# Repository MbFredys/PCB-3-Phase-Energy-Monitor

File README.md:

# Three-Phase Energy Monitor

Hardware design for a three-phase, four-wire energy-monitoring platform with Ethernet and Power over Ethernet, intended for future integration with building-management systems.

> **Project status:** Design and manufacturing documentation completed. The PCB has not been fabricated, calibrated, electrically validated, or tested for regulatory compliance.

## Project objective

The project explores an open and documented architecture capable of acquiring three-phase electrical measurements and exposing them through a connected embedded platform.

## System architecture

- **Measurement:** ATM90E32AS for 3P4W energy measurement
- **Controller:** ESP32-S3-MINI-1
- **Networking:** LAN8720A Ethernet PHY using RMII
- **Power:** TPS2378 PoE interface with local 5 V and 3.3 V rails
- **Sensing:** External current transformers and resistive voltage-sensing networks
- **Isolation:** Digital isolators between measurement and low-voltage digital domains
- **Development access:** USB and debugging/programming interfaces

## Engineering work

- Defined system requirements and functional architecture
- Selected the principal ICs, protection devices, connectors, and power components
- Developed the schematic and multi-domain PCB layout in KiCad
- Defined measurement, isolation, Ethernet, PoE, and power-distribution sections
- Prepared the BOM and manufacturing documentation

## Key design considerations

- Isolation boundaries and return-current paths
- Creepage and clearance around mains-related circuitry
- Mixed-signal grounding and decoupling
- Ethernet differential routing and PHY termination
- PoE power conversion and protection
- Calibration strategy for voltage and current channels

## Deliverables

The repository contains the available design source files and supporting manufacturing documentation. Review the repository structure before using any generated outputs.

## Validation still required

A physical prototype is required to verify:

- Electrical safety and isolation distances
- Measurement accuracy and calibration
- Ethernet and PoE operation
- Thermal behavior and power integrity
- EMC/EMI performance
- Compliance with any applicable product or installation standards

This repository should be treated as an engineering design project, not as a certified or production-ready energy meter.

## License

Licensed under CERN-OHL-W-2.0.

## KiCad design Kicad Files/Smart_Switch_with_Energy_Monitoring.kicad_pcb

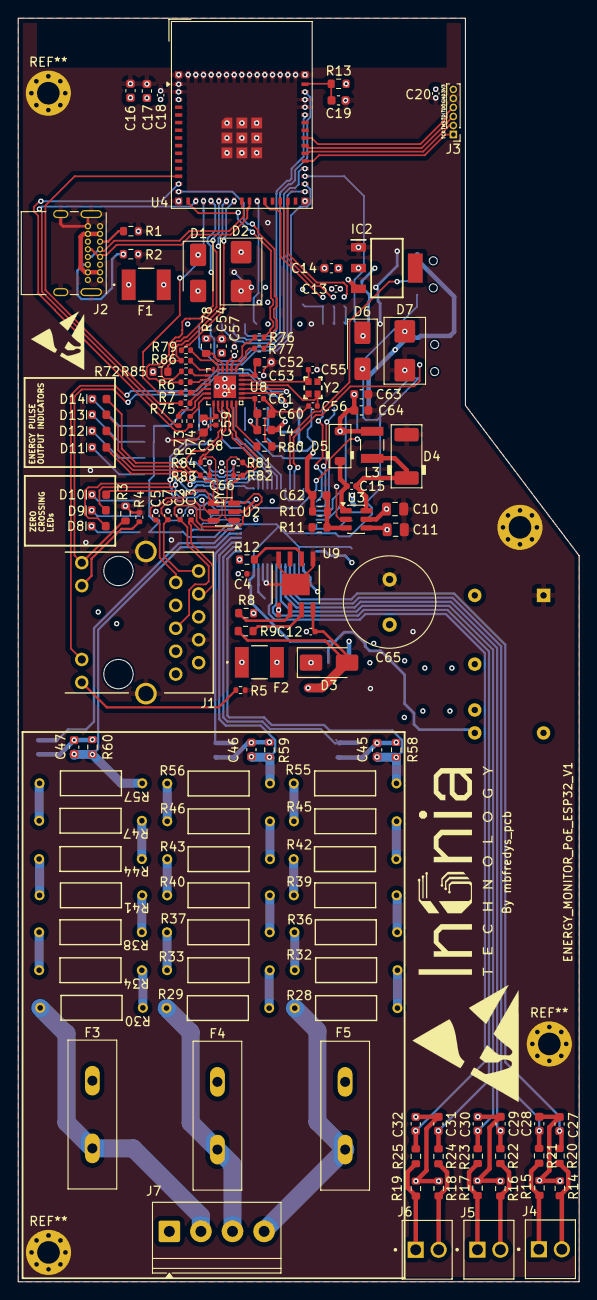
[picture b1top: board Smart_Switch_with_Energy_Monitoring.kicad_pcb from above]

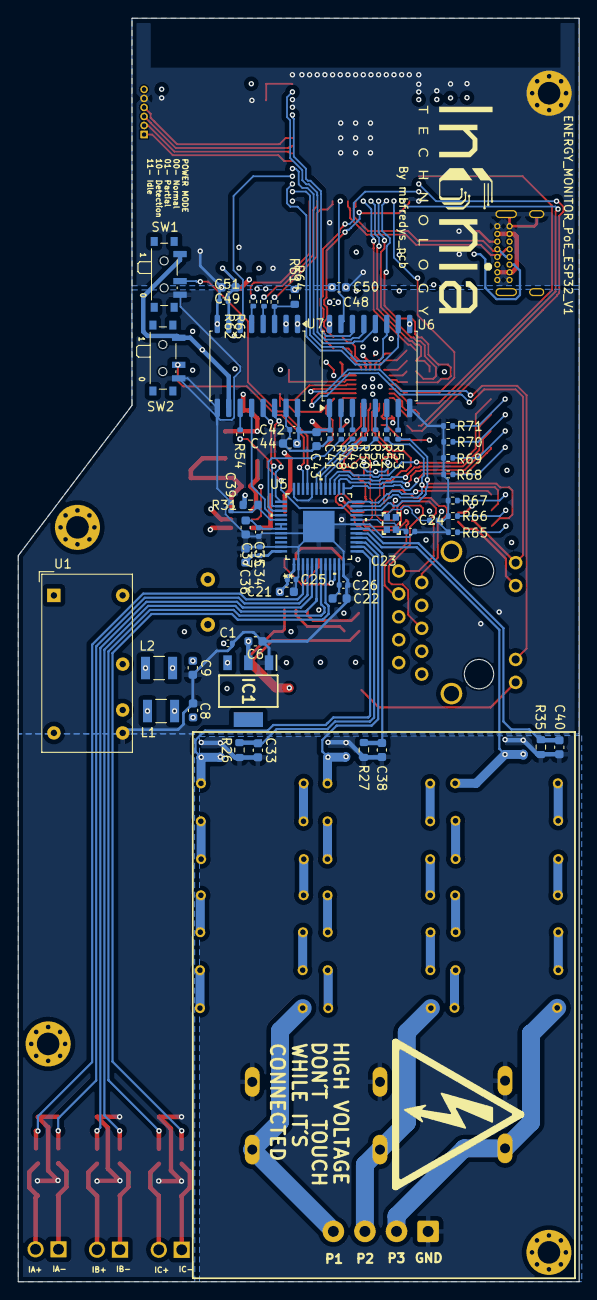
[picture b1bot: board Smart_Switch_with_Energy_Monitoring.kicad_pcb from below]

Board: 4 copper layers, 62.1 x 140.0 mm, 197 parts (58 on the bottom side), 153 nets.

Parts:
C1, C4, C12, C13, C15, C18, C20, C25, C26, C34, C35, C39, C41, C42, C48, C49, C57, C66: 0.1uF; C_0402_1005Metric
C2, C3, C5, C7, C23, C24, C55, C56: 10pF; C_0402_1005Metric
C6, C14, C16, C21, C36, C37, C43, C44, C50, C51, C54, C63, C64: 10uF; C_0603_1608Metric
C8, C9: 2.2uF; C_0603_1608Metric
C10, C11: 10uF; C_0805_2012Metric
C17, C19, C52, C58, C60: 1uF; C_0603_1608Metric
C22: 4.7uF; C_0603_1608Metric
C27, C28, C29, C30, C31, C32, C33, C38, C40, C45, C46, C47: 18nF; C_0603_1608Metric
C53, C59, C61: 470pF; C_0402_1005Metric
C62: 20pF; C_0603_1608Metric
C65: 22uF; C_Radial_D10.0mm_H12.5mm_P5.00mm
D1, D6: SS14; D_SMA
D2, D7: SMBJ5.0CA; D_SMB_TVS
D3: SMAJ58A; D_SMA
D4: SM360; D_MELF
D5: 1N4148W; D_SOD-123
D8, D9, D10, D11, D12, D13, D14: LEDs; LED_0603_1608Metric
F1: 1812L110PR; FUSE_1812L05060_LTF
F2: 1812L050/60MR; FUSE_1812L05060_LTF
F3, F4, F5: MOV14D471K
IC1, IC2: LD1117-3.3V; SOT230P700X180-4N
J1: RJ45_PoE; MagJack_PoE_RJ45
J2: USB_C_Receptacle_USB2.0_14P; USB_C_Receptacle_GCT_USB4085
J3: Pin Header; PinHeader_1x06_P1.00mm_Vertical
J4, J5, J6: Screw_Terminal_01x02; TE_282834-2
J7: Screw_Conn; TerminalBlock_Phoenix_PT-1,5-4-3.5-H_1x04_P3.50mm_Horizontal
L1, L2, L3: 22uH; FUSE_MF-USMFLAB
L4: FerriteBead; L_0603_1608Metric
R1, R2: 5.1k; R_0603_1608Metric
R3, R11, R12, R13, R31, R61, R78: 10k; R_0603_1608Metric
R4, R5: 270; R_0402_1005Metric
R6, R7, R48, R49, R50, R51, R62, R63, R64, R73, R74, R75, R76, R77, R79, R85, R86: 33; R_0402_1005Metric
R8: 24.9k; R_0603_1608Metric
R9: 63.4; R_0603_1608Metric
R10: 52.3k; R_0603_1608Metric
R14, R15, R16, R17, R18, R19: 2.4; R_0603_1608Metric
R20, R21, R22, R23, R24, R25, R26, R27, R35, R58, R59, R60: 1k; R_0603_1608Metric
R28, R29, R30, R32, R33, R34, R36, R37, R38, R39, R40, R41, R42, R43, R44, R45, R46, R47, R55, R56, R57: 240k; RES_09FCT00_VIS
R52, R53, R54, R65, R66, R67, R68, R69, R70, R71: 510; R_0402_1005Metric
R72: 2.2k; R_0603_1608Metric
R80: 12.1k; R_0603_1608Metric
R81, R82, R83, R84: 50; R_0402_1005Metric
SW1, SW2: SW_SPDT; SW_SPDT_PCM12
U1: NMA0505DC; Converter_DCDC_Murata_NMAxxxxDC_THT
U2: WE-TVS-824015043; SOT-23-6
U3: MCP16331x-xCH; SOT-23-6
U4: ESP32-S3-MINI-1; ESP32-S2-MINI-1
U5: ATM90E32AS-AU-Y; TQFP48_7x7MC_MCH
U6: Si8660ED-AS; SOIC-16W_7.5x10.3mm_P1.27mm
U7: Si8641ED-B-IS; SOIC-16W_7.5x10.3mm_P1.27mm
U8: LAN8720A
U9: TPS2378DDAR; DDA8_3P1X2P4_TEX-M
Y1: 16MHz; Crystal_SMD_2.0x1.6mm
Y2: 25MHz; Crystal_SMD_2.0x1.6mm

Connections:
+3.3V: C4.2, C14.2, C16.2, C17.2, C18.2, C20.2, C48.2, C49.2, C50.2, C51.2, C54.2, C57.2, IC2.2 (OUT), J1.4 (TCT), J1.5 (RCT), J3.6, L4.1, R13.2, R61.1, R72.2, U2.5 (VBUS), U4.3 (3V3), U6.16 (VDD2), U7.1 (VDD1), U7.7 (EN1), U8.9 (VDDIO)
+5V_SYS: C13.2, D1.1 (K), D2.2 (A), D6.1 (K), D7.2 (A), IC2.3 (IN), U1.14 (VIN+)
+48V: C10.2, C11.2, C12.2, C65.1, D3.1 (A1), F2.2, R8.1, R12.1, U3.4 (EN), U3.5 (V_{IN}), U9.1 (VDD)
/Communication Block/ESP32/LAN87_CRS_DV: R79.1, U4.22 (IO18)
/Communication Block/ESP32/LAN87_MDC: R85.1, U4.20 (IO16)
/Communication Block/ESP32/LAN87_MDIO: R72.1, R86.1, U4.21 (IO17)
/Communication Block/ESP32/LAN87_REFCLKO: R6.1, U4.19 (IO15)
/Communication Block/ESP32/LAN87_RXD0: R76.1, U4.16 (IO12)
/Communication Block/ESP32/LAN87_RXD1: R77.1, U4.15 (IO11)
/Communication Block/ESP32/LAN87_TXD0: R73.1, U4.17 (IO13)
/Communication Block/ESP32/LAN87_TXD1: R74.1, U4.14 (IO10)
/Communication Block/ESP32/LAN87_TXEN: R75.1, U4.13 (IO9)
/Communication Block/ESP32/LAN87_nRST: R7.1, U4.18 (IO14)
/Communication Block/LAN87/RJ45_LED1: J1.13 (GRN+), U8.3 (LED1/REGOFF)
/Communication Block/LAN87/RJ45_LED2: J1.11 (YLW+), R3.2, U8.2 (LED2/~INTSEL)
/Communication Block/LAN87/RJ45_RX+: C3.1, J1.3 (RD+), R82.2, U2.3 (I/O2), U8.23 (RXP)
/Communication Block/LAN87/RJ45_RX-: C2.1, J1.6 (RD-), R81.2, U2.1 (I/O1), U8.22 (RXN)
/Communication Block/LAN87/RJ45_TX+: C7.1, J1.1 (TD+), R84.2, U2.6 (I/O4), U8.21 (TXP)
/Communication Block/LAN87/RJ45_TX-: C5.1, J1.2 (TD-), R83.2, U2.4 (I/O3), U8.20 (TXN)
/Control Block/ESP32/ATM9_SPI_CS: R64.1, U4.26 (IO26)
/Control Block/ESP32/ATM9_SPI_MISO: U4.25 (IO21), U6.15 (B1)
/Control Block/ESP32/ATM9_SPI_MOSI: R62.1, U4.29 (IO34)
/Control Block/ESP32/ATM9_SPI_SCLK: R63.1, U4.28 (IO33)
/Control Block/ESP32/ATM90_INT_RQ0: U4.44 (IO46), U6.13 (B3)
/Control Block/ESP32/ATM90_INT_RQ1: U4.41 (IO45), U6.14 (B2)
/Control Block/ESP32/ATM90_WarnOut: U4.34 (IO38), U6.12 (B4)
/Control Block/ESP32/ATM90_ZX0: U4.31 (IO35), U6.11 (B5)
/Control Block/ESP32/ATM90_ZX1: U4.32 (IO36), U6.10 (B6)
/Control Block/ESP32/ATM90_ZX2: U4.33 (IO37), U7.6 (A4)
/Control Block/ESP32/USB_D+: J2.A7 (D-), J2.B7 (D-), U4.24 (USB_D+)
/Control Block/ESP32/USB_D-: J2.A6 (D+), J2.B6 (D+), U4.23 (USB_D-)
/Control Block/JTAG_TCK: J3.1, U4.35 (IO39)
/Control Block/JTAG_TDI: J3.3, U4.37 (IO41)
/Control Block/JTAG_TDO: J3.4, U4.38 (IO42)
/Control Block/JTAG_TMS: J3.2, U4.36 (IO40)
/Energy Measurement Block/CF1: D11.2 (A), U5.25 (CF1)
/Energy Measurement Block/CF2: D12.2 (A), U5.26 (CF2)
/Energy Measurement Block/CF3: D13.2 (A), U5.27 (CF3)
/Energy Measurement Block/CF4: D14.2 (A), U5.28 (CF4)
/Energy Measurement Block/IAN: C28.2, R21.1, U5.4 (I1N)
/Energy Measurement Block/IAP: C27.1, R20.1, U5.3 (I1P)
/Energy Measurement Block/IBN: C30.2, R23.1, U5.6 (I2N)
/Energy Measurement Block/IBP: C29.1, R22.1, U5.5 (I2P)
/Energy Measurement Block/ICN: C32.2, R25.1, U5.8 (I3N)
/Energy Measurement Block/ICP: C31.1, R24.1, U5.7 (I3P)
/Energy Measurement Block/PM0: SW1.2 (B), U5.33 (PM0)
/Energy Measurement Block/PM1: SW2.2 (B), U5.34 (PM1)
/Energy Measurement Block/VAN: C33.1, R26.2, U5.14 (V1N)
/Energy Measurement Block/VAP: C45.1, R55.1, R58.2, U5.13 (V1P)
/Energy Measurement Block/VBN: C38.1, R27.2, U5.16 (V2N)
/Energy Measurement Block/VBP: C46.1, R56.1, R59.2, U5.15 (V2P)
/Energy Measurement Block/VCN: C40.1, R35.2, U5.18 (V3N)
/Energy Measurement Block/VCP: C47.1, R57.1, R60.2, U5.17 (V3P)
/Energy Measurement Block/WarnOut: R51.2, U5.29 (WarnOut)
/Energy Measurement Block/ZX0: D8.2 (A), R53.2, U5.22 (ZX0)
/Energy Measurement Block/ZX1: D9.2 (A), R52.2, U5.23 (ZX1)
/Energy Measurement Block/ZX2: D10.2 (A), R54.2, U5.24 (ZX2)
/Power Block/RJ45/TPS23_VDC+: F2.1, J1.9 (PW+)
/Power Block/RJ45/TPS23_VDC-: C12.1, D3.2 (A2), J1.10 (PW-), R9.1, U9.4 (VSS)
GND: C2.2, C3.2, C4.1, C5.2, C7.2, C10.1, C11.1, C13.1, C14.1, C16.1, C17.1, C18.1, C19.1, C20.1, C48.1, C49.1, C50.1, C51.1, C52.1, C53.2, C54.1, C55.1, C56.1, C57.1, C58.1, C59.2, C60.1, C61.2, C63.1, C64.1, C65.2, C66.1, D2.1 (K), D4.2 (A), D7.1 (K), IC2.1 (ADJ), J1.7 (GND), J1.S1 (SHLD), J1.S2 (SHLD), J2.A1 (GND), J2.A12 (GND), J2.B1 (GND), J2.B12 (GND), J2.S1 (SHIELD), J3.5, R1.2, R2.2, R3.1, R4.2, R5.2, R11.2, R78.2, R80.1, U1.1 (VIN-), U2.2 (GND), U3.2 (GND), U4.1 (GND), U4.2 (GND), U4.42 (GND), U4.43 (GND), U4.46 (GND), U4.47 (GND), U4.48 (GND), U4.49 (GND), U4.50 (GND), U4.51 (GND), U4.52 (GND), U4.53 (GND), U4.54 (GND), U4.55 (GND), U4.56 (GND), U4.57 (GND), U4.58 (GND), U4.59 (GND), U4.60 (GND), U4.61 (GND), U4.62 (GND), U4.63 (GND), U4.64 (GND), U4.65 (GND), U5.9 (IC), U5.10 (IC), U6.9 (GND2), U7.2 (GND1), U7.8 (GND1), U8.25 (VSS), U9.5 (RTN), U9.8 (APD), U9.EPAD
ISO_+3.3V: C6.2, C21.2, C25.2, C34.2, C36.2, C41.2, C42.2, C43.2, C44.2, IC1.2 (OUT), R31.1, SW1.1 (A), SW2.1 (A), U5.1 (AVDD), U5.48 (DVDD), U6.1 (VDD1), U7.10 (EN2), U7.16 (VDD2)
ISO_+5V: C1.2, C8.1, IC1.3 (IN), L1.2
ISO_GND: C1.1, C6.1, C8.2, C9.1, C21.1, C22.2, C23.1, C24.1, C25.1, C26.1, C27.2, C28.1, C29.2, C30.1, C31.2, C32.1, C34.1, C35.1, C36.1, C37.1, C39.1, C41.1, C42.1, C43.1, C44.1, IC1.1 (ADJ), R14.1, R15.2, R16.1, R17.2, R18.1, R19.2, R65.1, R66.1, R67.1, R68.1, R69.1, R70.1, R71.1, SW1.3 (C), SW2.3 (C), U1.8 (0V), U5.2 (AGND), U5.12 (AGND), U5.19 (DGND), U5.32 (TEST), U5.36 (IC), U5.44 (DGND), U5.47 (DGND), U5.EPAD, U6.8 (GND1), U7.9 (GND2), U7.15 (GND2)
unnamed: C9.2, L2.2
unnamed: C35.2, C37.2, U5.42 (VDD18), U5.43 (VDD18)
unnamed: C66.2, R81.1, R82.1, R83.1, R84.1
unnamed: D1.2 (A), F1.2
unnamed: C15.1, D4.1 (K), L3.1, U3.6 (SW)
unnamed: C62.2, C63.2, C64.2, D5.2 (A), D6.2 (A), L3.2, R10.2
unnamed: C15.2, D5.1 (K), U3.1 (BOOST)
unnamed: D8.1 (K), R65.2
unnamed: D9.1 (K), R66.2
unnamed: D10.1 (K), R67.2
unnamed: D11.1 (K), R68.2
unnamed: D12.1 (K), R69.2
unnamed: D13.1 (K), R70.2
unnamed: D14.1 (K), R71.2
unnamed: F1.1, J2.A4 (VBUS), J2.A9 (VBUS), J2.B4 (VBUS), J2.B9 (VBUS)
unnamed: F3.2, J7.2, R30.2
unnamed: F4.2, J7.3, R29.2
unnamed: F5.2, J7.4, R28.2
unnamed: J1.14 (GRN-), R5.1
unnamed: J1.12 (YLW-), R4.1
unnamed: J2.A5 (CC1), R1.1
unnamed: J2.B5 (CC2), R2.1
unnamed: J4.1, R15.1, R21.2
unnamed: J4.2, R14.2, R20.2
unnamed: J5.1, R17.1, R23.2
unnamed: J5.2, R16.2, R22.2
unnamed: J6.1, R19.1, R25.2
unnamed: J6.2, R18.2, R24.2
unnamed: R28.1, R32.2
unnamed: R29.1, R33.2
unnamed: R30.1, R34.2
unnamed: R32.1, R36.2
unnamed: R33.1, R37.2
unnamed: R34.1, R38.2
unnamed: R36.1, R39.2
unnamed: R37.1, R40.2
unnamed: R38.1, R41.2
unnamed: R39.1, R42.2
unnamed: R40.1, R43.2
unnamed: R41.1, R44.2
unnamed: R42.1, R45.2
unnamed: R43.1, R46.2
unnamed: R44.1, R47.2
unnamed: R45.1, R55.2
unnamed: R46.1, R56.2
unnamed: R47.1, R57.2
unnamed: L1.1, U1.9 (VOUT+)
unnamed: L2.1, U1.11 (VOUT-)
unnamed: C62.1, R10.1, R11.1, U3.3 (V_{FB})
unnamed: C19.2, R13.1, U4.45 (EN)
unnamed: U5.37 (*CS), U7.14 (B1)
unnamed: C39.2, R31.2, U5.41 (*RESET)
unnamed: R50.2, U5.30 (IRQ0)
unnamed: R49.2, U5.31 (IRQ1)
unnamed: C23.2, U5.20 (OSCI), Y1.1
unnamed: C24.2, U5.21 (OSCO), Y1.2
unnamed: U5.38 (SCLK), U7.13 (B2)
unnamed: U5.40 (SDI), U7.12 (B3)
unnamed: R48.2, U5.39 (SDO)
unnamed: C22.1, C26.2, U5.11 (Vref)
unnamed: R48.1, U6.2 (A1)
unnamed: R49.1, U6.3 (A2)
unnamed: R50.1, U6.4 (A3)
unnamed: R51.1, U6.5 (A4)
unnamed: R52.1, U6.6 (A5)
unnamed: R53.1, U6.7 (A6)
unnamed: R61.2, R64.2, U7.3 (A1)
unnamed: R63.2, U7.4 (A2)
unnamed: R62.2, U7.5 (A3)
unnamed: R54.1, U7.11 (B4)
unnamed: R79.2, U8.11 (CRS_DV/MODE2)
unnamed: R85.2, U8.13 (MDC)
unnamed: R86.2, U8.12 (MDIO)
unnamed: R80.2, U8.24 (RBIAS)
unnamed: R76.2, U8.8 (RXD0/MODE0)
unnamed: R77.2, U8.7 (RXD1/MODE1)
unnamed: R78.1, U8.10 (RXER/PHYAD0)
unnamed: R73.2, U8.17 (TXD0)
unnamed: R74.2, U8.18 (TXD1)
unnamed: R75.2, U8.16 (TXEN)
unnamed: C58.2, C59.1, C60.2, C61.1, L4.2, U8.1 (VDD2A), U8.19 (VDD1A)
unnamed: C52.2, C53.1, U8.6 (VDDCR)
unnamed: C55.2, U8.5 (XTAL1/CLKIN), Y2.1
unnamed: C56.2, U8.4 (XTAL2), Y2.2
unnamed: R6.2, U8.14 (~INT/REFCLKO)
unnamed: R7.2, U8.15 (~RST)
unnamed: R12.2, U9.6 (CDB)
unnamed: R9.2, U9.3 (CLS)
unnamed: R8.2, U9.2 (DEN)
P_GND: C33.2, C38.2, C40.2, C45.2, C46.2, C47.2, F3.1, F4.1, F5.1, J7.1, R26.1, R27.1, R35.1, R58.1, R59.1, R60.1

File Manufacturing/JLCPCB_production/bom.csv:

Designator,Footprint,Quantity,Value,LCSC Part #
"C1, C12, C13, C15, C18, C20, C25, C26, C34, C35, C39, C4, C41, C42, C48, C49, C57, C66",0402,18,0.1uF,
"C10, C11",0805,2,10uF,
"C14, C16, C21, C36, C37, C43, C44, C50, C51, C54, C6, C63, C64",0603,13,10uF,
"C17, C19, C52, C58, C60",0603,5,1uF,
"C2, C23, C24, C3, C5, C55, C56, C7",0402,8,10pF,
C22,0603,1,4.7uF,
"C27, C28, C29, C30, C31, C32, C33, C38, C40, C45, C46, C47",0603,12,18nF,
"C53, C59, C61",0402,3,470pF,
C62,0603,1,20pF,
C65,C_Radial_D10.0mm_H12.5mm_P5.00mm,1,22uF,
"C8, C9",0603,2,2.2uF,
"D1, D6",D_SMA,2,SS14,
"D10, D11, D12, D13, D14, D8, D9",0603,7,LEDs,
"D2, D7",D_SMB_TVS,2,SMBJ5.0CA,
D3,D_SMA,1,SMAJ58A,
D4,D_MELF,1,SM360,
D5,D_SOD-123,1,1N4148W,
F1,FUSE_1812L05060_LTF,1,1812L110PR,
F2,FUSE_1812L05060_LTF,1,1812L050/60MR,
"F3, F4, F5",MOV14D471K,3,MOV14D471K,
"IC1, IC2",SOT230P700X180-4N,2,LD1117-3.3V,
J1,MagJack_PoE_RJ45,1,RJ45_PoE,
J2,USB_C_Receptacle_GCT_USB4085,1,USB_C_Receptacle_USB2.0_14P,
J3,PinHeader_1x06_P1.00mm_Vertical,1,Pin Header,
"J4, J5, J6",TE_282834-2,3,Screw_Terminal_01x02,
J7,"TerminalBlock_Phoenix_PT-1,5-4-3.5-H_1x04_P3.50mm_Horizontal",1,Screw_Conn,
"L1, L2, L3",FUSE_MF-USMFLAB,3,22uH,
L4,0603,1,FerriteBead,
"R1, R2",0603,2,5.1k,
R10,0603,1,52.3k,
"R11, R12, R13, R3, R31, R61, R78",0603,7,10k,
"R14, R15, R16, R17, R18, R19",0603,6,2.4,
"R20, R21, R22, R23, R24, R25, R26, R27, R35, R58, R59, R60",0603,12,1k,
"R28, R29, R30, R32, R33, R34, R36, R37, R38, R39, R40, R41, R42, R43, R44, R45, R46, R47, R55, R56, R57",RES_09FCT00_VIS,21,240k,
"R4, R5",0402,2,270,
"R48, R49, R50, R51, R6, R62, R63, R64, R7, R73, R74, R75, R76, R77, R79, R85, R86",0402,17,33,
"R52, R53, R54, R65, R66, R67, R68, R69, R70, R71",0402,10,510,
R72,0603,1,2.2k,
R8,0603,1,24.9k,
R80,0603,1,12.1k,
"R81, R82, R83, R84",0402,4,50,
R9,0603,1,63.4,
"SW1, SW2",SW_SPDT_PCM12,2,SW_SPDT,
U1,Converter_DCDC_Murata_NMAxxxxDC_THT,1,NMA0505DC,
U2,SOT-23-6,1,WE-TVS-824015043,
U3,SOT-23-6,1,MCP16331x-xCH,
U4,ESP32-S2-MINI-1,1,ESP32-S3-MINI-1,
U5,TQFP48_7x7MC_MCH,1,ATM90E32AS-AU-Y,
U6,SOIC-16W_7.5x10.3mm_P1.27mm,1,Si8660ED-AS,
U7,SOIC-16W_7.5x10.3mm_P1.27mm,1,Si8641ED-B-IS,
U8,LAN8720A,1,LAN8720A,
U9,DDA8_3P1X2P4_TEX-M,1,TPS2378DDAR,
Y1,Crystal_SMD_2.0x1.6mm,1,16MHz,
Y2,Crystal_SMD_2.0x1.6mm,1,25MHz,

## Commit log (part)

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2025-11-18 Revise README for Energy Monitoring PCB project
    Updated project description, features, and usage instructions in README.md for clarity and detail.
2025-11-18 Simplify license section in README
    Removed redundant license section and added emoji.
2025-11-18 Fix overview section formatting in README
    Updated overview section formatting in README.
2025-11-18 Simplify power architecture description in README
2025-12-01 Update LICENSE
2025-12-01 Add CERN Open Hardware Licence V2 to COPYING
    Added CERN Open Hardware Licence Version 2 - Weakly Reciprocal to the COPYING file.
2025-12-01 Update project license to CERN Open Hardware Licence
2025-12-01 Add CERN OHL W 2.0 license badge
    Added license badge to README

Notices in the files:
README.md:
License: CERN-OHL-W-2.0
